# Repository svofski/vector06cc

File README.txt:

VECTOR-06C FPGA REPLICA
	~~~~~~~~~~~~~~~~~~~~~~~

This project is an attempt to replicate Vector-06C, a Soviet-era home 
computer, in FPGA. The primary hardware platform for this project is 
Altera DE1 development board.

CONTENTS

* Features
* DE1 Thingies
* DE1 SRAM Mapping and Starter Kit Utility
* Known Problems
* Known ROMs That Have Issues
* Acknowledgements

Features
~~~~~~~~

The following features are implemented as of December 16, 2007:

- CPU
- SRAM is used for everything
- 8253 timer (not entirely, only what's useful for sound generation)
- tape i/o (and beeper)
- all internal stuff, video modes, palette
- PS/2 keyboard
- 256K RAM disk
- DE1 JTAG interface to JTAG USB API program

DE1 Thingies
~~~~~~~~~~~~

Enjoy the generous blinkenlights from Terasic and svofski!

It is important to have switches SW8 and SW9 in "1" position (up). This
enables proper CPU clocking. Other switches just change the blinken pattern
and only important when you're debugging.

KEY0 is master reset, somewhat like BLK+VVOD. 

KEY1 is manual clock for CPU. Useful only for hardcore debugging.

KEY3 is same as BLK+SBR: boot ROM is disabled, RST0 is executed.

If KEY3 is held pressed when KEY0 is being pressed, or when Vector-06C 
image is being programmed into FPGA, boot ROM doesn't work at all. 
This is useful if you want to preserve SRAM content.

DE1 SRAM Mapping
~~~~~~~~~~~~~~~~
DE1 SRAM is addressed by word. This is mapped linearly into bytes, so programs
can be uploaded with CII Starter Kit Control Panel software without any 
modifications. However, addresses should be minded.

Normally a .rom file goes to address 0x0100. Translated into word-address, that
becomes 0x0080. So when uploading a .rom file to Vector, enter "80" in the SRAM
page, "Sequential Write" box.

Similarly, RAM disk pages start after first 64K, which is 0x10000, or 0x8000 
in words. So, for uploading RAM disk images, use address "8000". RAM disk images
can be read Starter Kit Control Panel software and re-uploaded later or used
with an emulator as .edd files.

Known Problems
~~~~~~~~~~~~~~

1. Keyboard input gets stuck when some of the ":()*@" characters are entered.

	This is a problem with PS/2 -> Vector keyboard key/char mapping.
	I tried to make it as much PS/2 as possible. But since some characters
	shift/key combination differ, there's more than one direct mapping and
	this mapping gets stuck.
	
	Workaround: always carefully press SHIFT, then ":", then release ":", 
	then release SHIFT. If input gets stuck, unstuck it by carefully 
	pressing same character again.

2. PS key is not implemented

	Well, duh.. 

3. BLK+VVOD is not implemented

	Use KEY0 instead.

4. AY-3-WTF is not implemented

n-1. ROM "<whatever>.rom" doesn't work
	
	Unless you know for sure that it must work, screw it.

n. ROM "<whatver>.rom" works incorrectly.

	If you know for sure how it must work, I'm open for suggestions.

Known ROMs That Have Issues
~~~~~~~~~~~~~~~~~~~~~~~~~~~
81dca11bea7fb69a1226a170f1f47e85 *EXOLON.ROM
		Jerky border and keyboard input doesn't work, no known workaround

b27de9107eba6a1d9fb43e92e281099e *MUSICIAN.ROM
		Vertical scrolling is screwed up, depends on keys pressed.
		I studied the code and can't see how it can behave differently.

Acknowledgements
~~~~~~~~~~~~~~~~

This project uses work of different people. 

T80 CPU by Daniel Wallner with fixes from MikeJ of www.fpgaarcade.com is used 
for KR580WM80A. The code is modified in attempt to make this otherwise
excellent CPU cycle-compatible with i8080 and to implement STACK signal in PSW.

82C55 code by MikeJ of www.fpgaarcade.com is used without any modifications.

DE1-specific code uses, or may be based upon, samples from Altera DE1 package.

Special thanks to Alexander Timoshenko for documentation and general information
about Vector-06C, Dmitry Tselikov for hints and good reference emulator, Roman
Panteleev and Artem Navalon for ve27a with debugger.

$Id$

Viacheslav Slavinsky
http://sensi.org/~svo
http://sensi.org/~svo/vector06c

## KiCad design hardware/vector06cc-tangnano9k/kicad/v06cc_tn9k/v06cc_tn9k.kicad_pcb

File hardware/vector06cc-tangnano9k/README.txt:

vector06cc-specific carrier board for Tang Nano 9k

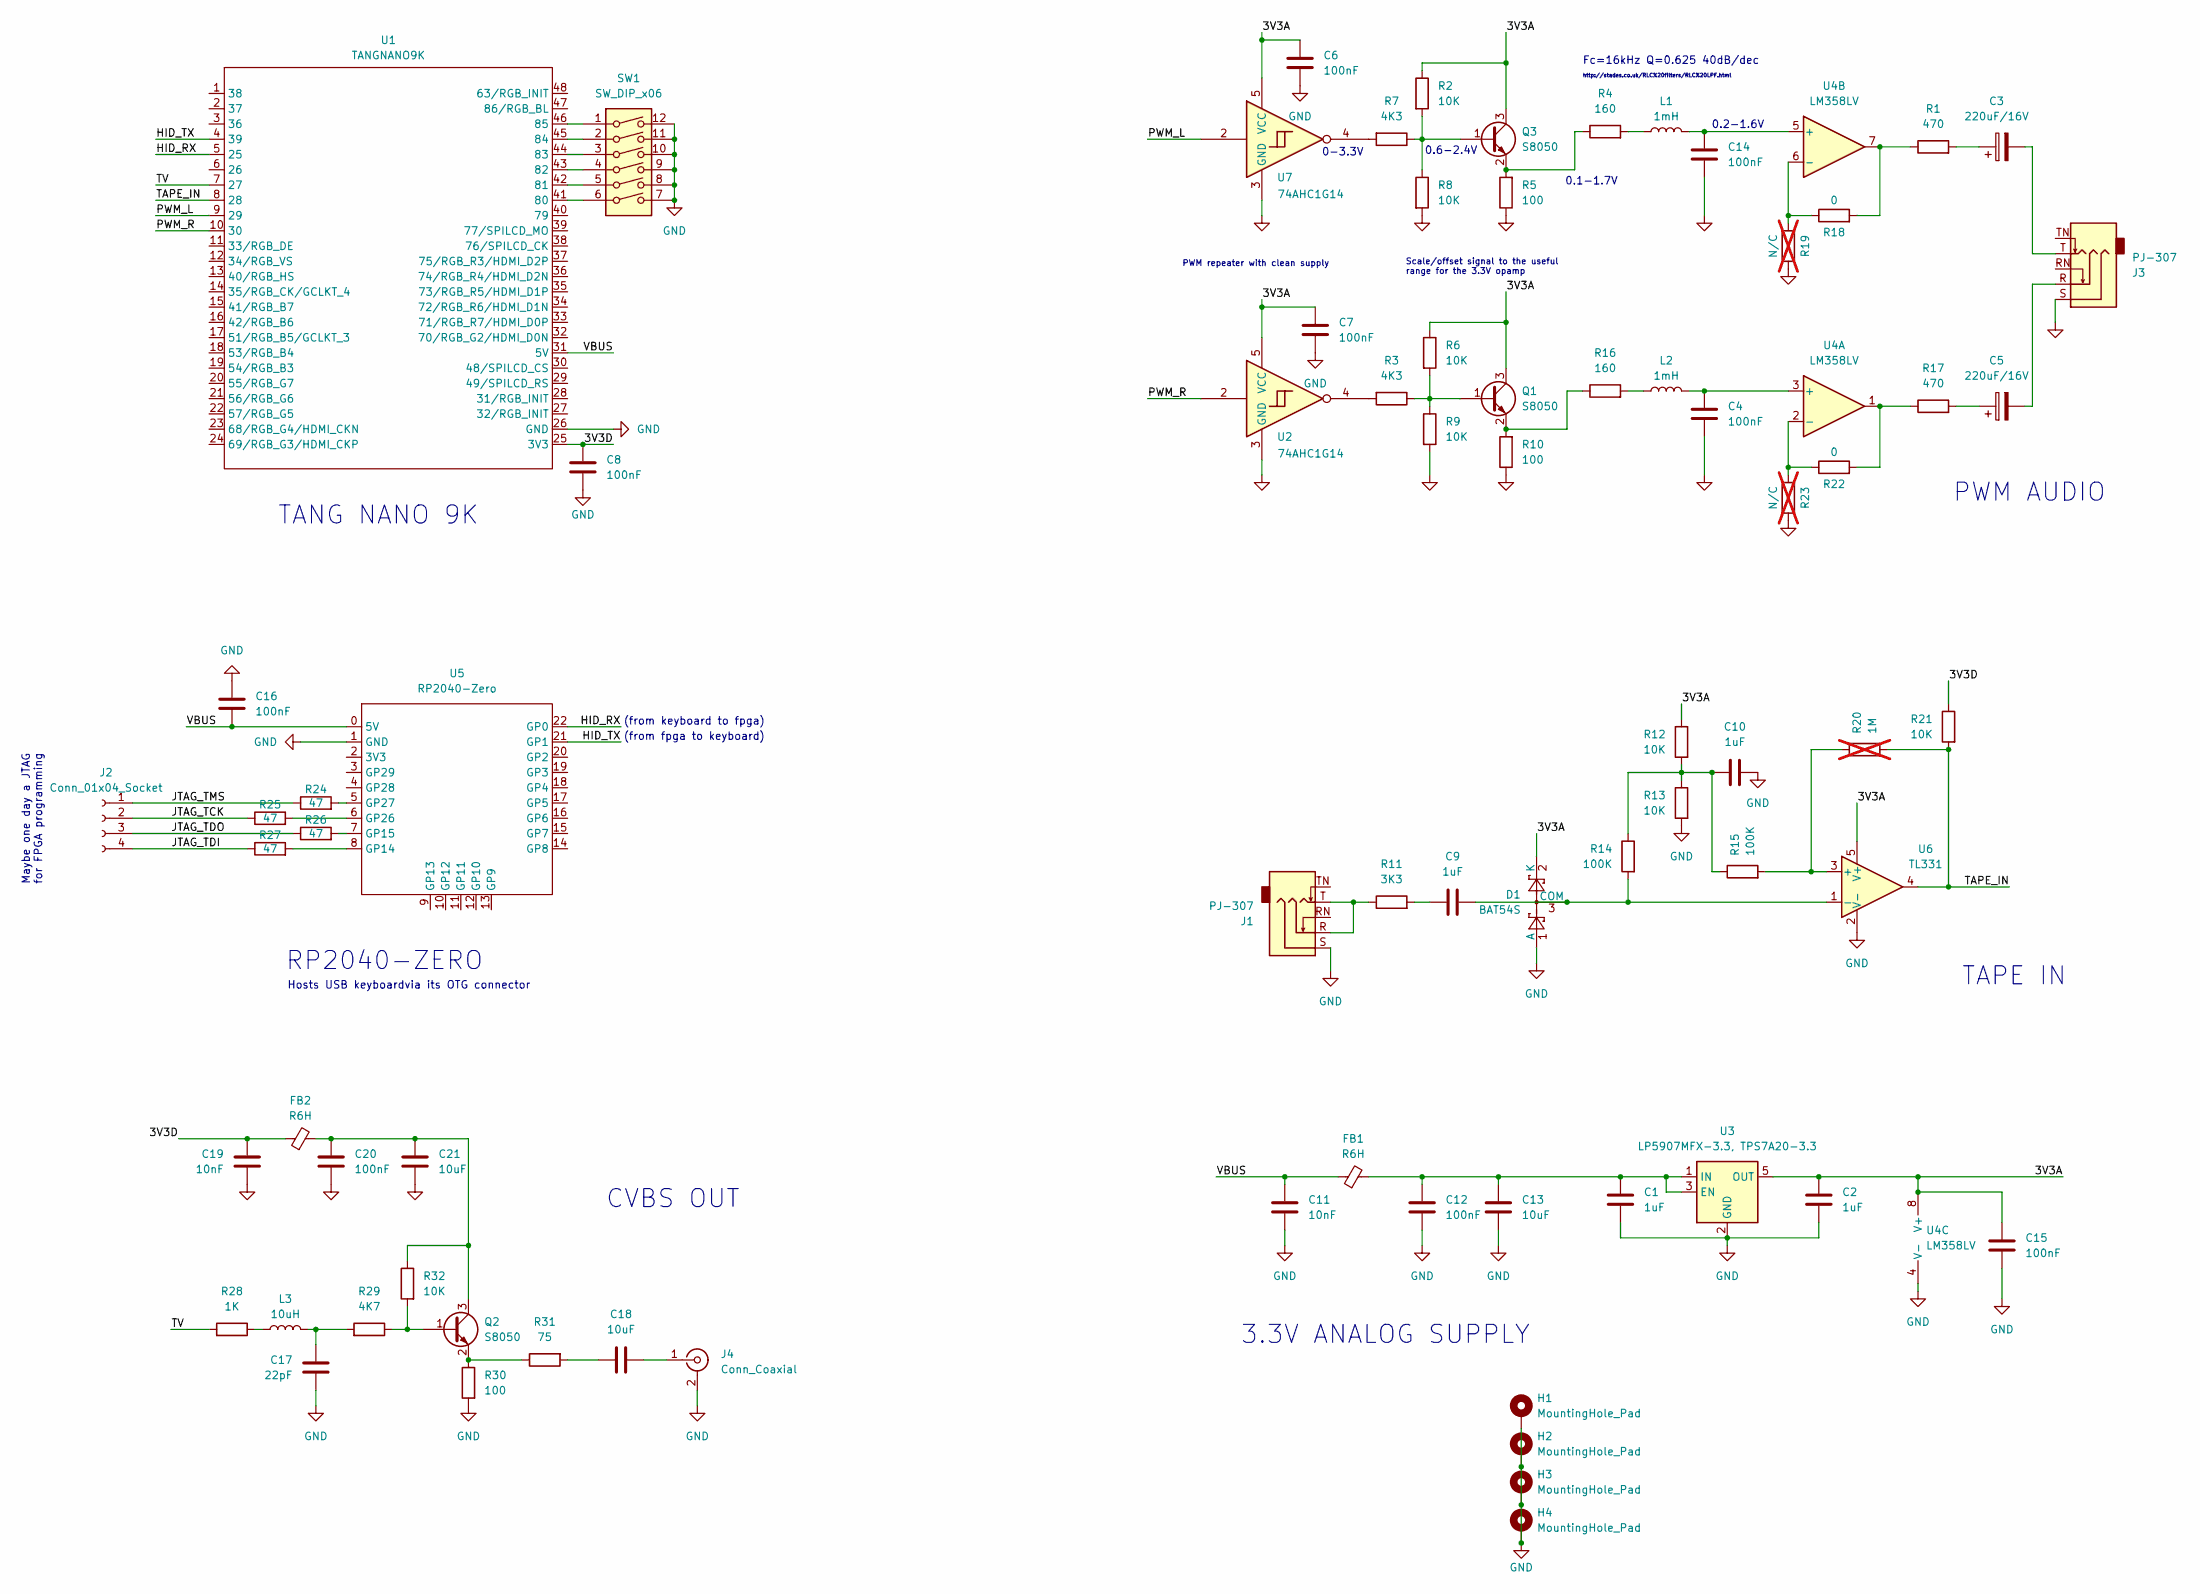
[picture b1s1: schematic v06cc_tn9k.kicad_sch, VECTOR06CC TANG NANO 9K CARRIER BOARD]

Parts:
C1, C2, C9, C10: 1uF; C_0805_2012Metric
C3, C5: 220uF/16V; CP_Elec_6.3x7.7
C4, C6, C7, C8, C12, C14, C15, C16, C20: 100nF; C_0603_1608Metric
C11, C19: 10nF; C_0805_2012Metric
C13, C18, C21: 10uF; C_0805_2012Metric
C17: 22pF; C_0603_1608Metric
D1: BAT54S; SOT-23
FB1, FB2: R6H; L_Radial_D6.0mm_P4.00mm
H1, H2, H3, H4: MountingHole_Pad; MountingHole_3.2mm_M3_DIN965_Pad
J1, J3: PJ-307; Jack_3.5mm_CUI_SJ1-3525N_Horizontal
J2: Conn_01x04_Socket; PinSocket_1x04_P2.54mm_Vertical
J4: Conn_Coaxial; CUI_RCJ-013
L1, L2: 1mH; L_Radial_D7.2mm_P3.00mm_Murata_1700
L3: 10uH; L_0805_2012Metric
Q1, Q2, Q3: S8050; SOT-23
R1, R17: 470; R_0805_2012Metric
R2, R6, R8, R9, R12, R13, R21, R32: 10K; R_0805_2012Metric
R3, R7: 4K3; R_0805_2012Metric
R4, R16: 160; R_0805_2012Metric
R5, R10, R30: 100; R_0805_2012Metric
R11: 3K3; R_0805_2012Metric
R14, R15: 100K; R_0805_2012Metric
R18, R22: 0; R_0805_2012Metric
R19, R23: N/C; R_0805_2012Metric; not fitted
R20: 1M; R_0805_2012Metric; not fitted
R24, R25, R26, R27: 47; R_0805_2012Metric
R28: 1K; R_0805_2012Metric
R29: 4K7; R_0805_2012Metric
R31: 75; R_0805_2012Metric
SW1: SW_DIP_x06; SW_DIP_SPSTx06_Slide_9.78x17.42mm_W7.62mm_P2.54mm
U1: TANGNANO9K; TangNano9k
U2, U7: 74AHC1G14; SOT-23-5
U3: LP5907MFX-3.3, TPS7A20-3.3; SOT-23-5
U4: LM358LV; SOIC-8_3.9x4.9mm_P1.27mm
U5: RP2040-Zero; rp2040-zero
U6: TL331; SOT-23-5

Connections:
/3V3A: C2.1, C6.2, C7.2, C15.2, D1.2 (K), Q1.3 (C), Q3.3 (C), R2.1, R6.1, R12.1, U2.5 (VCC), U3.5 (OUT), U4.8 (V+), U6.5 (V+), U7.5 (VCC)
/3V3D: C8.2, C19.1, FB2.1, R21.1, U1.25 (3V3)
/HID_RX: U1.5 (25), U5.22 (GP0)
/HID_TX: U1.4 (39), U5.21 (GP1)
/JTAG_TCK: J2.2, R25.1
/JTAG_TDI: J2.4, R27.1
/JTAG_TDO: J2.3, R26.1
/JTAG_TMS: J2.1, R24.1
/PWM_L: U1.9 (29), U7.2
/PWM_R: U1.10 (30), U2.2
/TAPE_IN: R20.2, R21.2, U1.8 (28), U6.4
/TV: R28.2, U1.7 (27)
/VBUS: C11.1, C16.1, FB1.1, U1.31 (5V), U5.0 (5V)
GND: C1.2, C2.2, C4.1, C6.1, C7.1, C8.1, C10.2, C11.2, C12.2, C13.2, C14.1, C15.1, C16.2, C17.1, C19.2, C20.2, C21.2, D1.1 (A), H1.1, H2.1, H3.1, H4.1, J1.S, J3.S, J4.2 (Ext), R5.1, R8.2, R9.2, R10.1, R13.2, R19.1, R23.1, R30.2, SW1.7, SW1.8, SW1.9, SW1.10, SW1.11, SW1.12, U1.26 (GND), U2.3 (GND), U3.2 (GND), U4.4 (V-), U5.1 (GND), U6.2 (V-), U7.3 (GND)
unnamed: C3.1, R1.2
unnamed: C3.2, J3.T
unnamed: C5.1, R17.2
unnamed: C5.2, J3.R
unnamed: C9.1, R11.2
unnamed: C10.1, R12.2, R13.1, R14.1, R15.1
unnamed: C17.2, L3.1, R29.2
unnamed: C18.1, R31.2
unnamed: C9.2, D1.3 (COM), R14.2, U6.1 (-)
unnamed: J1.R, J1.T, R11.1
unnamed: C18.2, J4.1 (In)
unnamed: L1.1, R4.2
unnamed: L2.1, R16.2
unnamed: L3.2, R28.1
unnamed: Q1.1 (B), R3.1, R6.2, R9.1
unnamed: Q1.2 (E), R10.2, R16.1
unnamed: Q2.1 (B), R29.1, R32.2
unnamed: C20.1, C21.1, FB2.2, Q2.3 (C), R32.1
unnamed: Q2.2 (E), R30.1, R31.1
unnamed: Q3.1 (B), R2.2, R7.1, R8.1
unnamed: Q3.2 (E), R4.1, R5.2
unnamed: R1.1, R18.2, U4.7
unnamed: R3.2, U2.4
unnamed: R7.2, U7.4
unnamed: R17.1, R22.2, U4.1
unnamed: SW1.6, U1.41 (80)
unnamed: SW1.5, U1.42 (81)
unnamed: SW1.4, U1.43 (82)
unnamed: SW1.3, U1.44 (83)
unnamed: SW1.2, U1.45 (84)
unnamed: SW1.1, U1.46 (85)
unnamed: C1.1, C12.1, C13.1, FB1.2, U3.1 (IN), U3.3 (EN)
unnamed: C4.2, L2.2, U4.3 (+)
unnamed: R22.1, R23.2, U4.2 (-)
unnamed: C14.2, L1.2, U4.5 (+)
unnamed: R18.1, R19.2, U4.6 (-)
unnamed: R27.2, U5.8 (GP14)
unnamed: R26.2, U5.7 (GP15)
unnamed: R25.2, U5.6 (GP26)
unnamed: R24.2, U5.5 (GP27)
unnamed: R15.2, R20.1, U6.3 (+)

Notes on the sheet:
PWM AUDIO
Hosts USB keyboardvia its OTG connector
(from keyboard to fpga)
http://stades.co.uk/RLC%20filters/RLC%20LPF.html
Maybe one day a JTAG for FPGA programming
3.3V ANALOG SUPPLY
0.6-2.4V
0.2-1.6V
Scale/offset signal to the useful range for the 3.3V opamp
PWM repeater with clean supply
(from fpga to keyboard)
0.1-1.7V
RP2040-ZERO
Fc=16kHz Q=0.625 40dB/dec
TAPE IN
0-3.3V
CVBS OUT
TANG NANO 9K

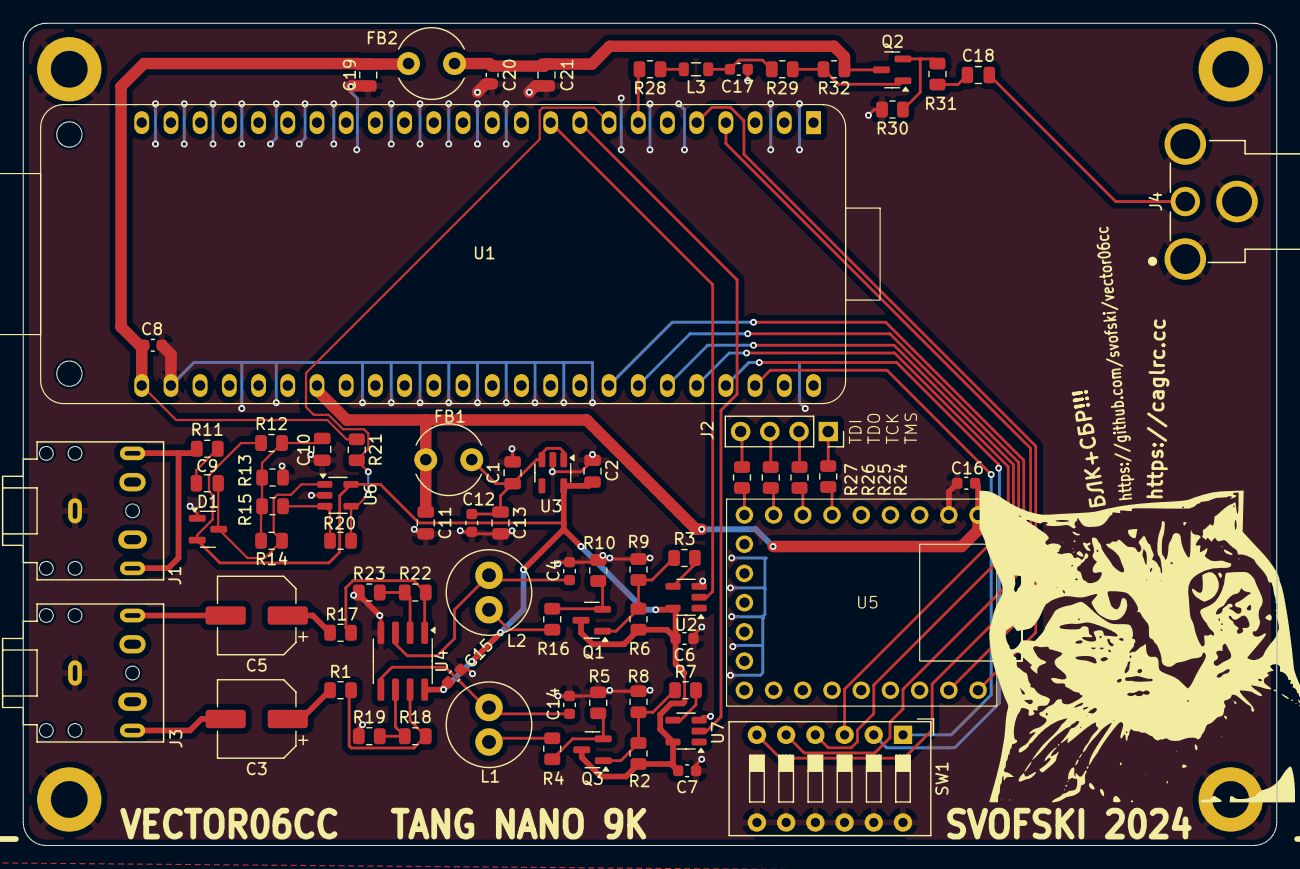
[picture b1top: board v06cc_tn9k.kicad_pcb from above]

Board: 2 copper layers, 109.0 x 71.5 mm, 78 parts (0 on the bottom side), 55 nets.

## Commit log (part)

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2008-01-26 fill last page of file selector
2008-01-26 Edited wiki page through web user interface.
2008-01-27 compilable without floppy or osd
2008-01-29 in i82c55 -- uncommented port clear on mode set; musician.rom doesn't jump its screen then, can't be 100% sure about the rest ay -- fixed reading from registers moved out fake 8255 "pu" to a separate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
2008-01-30 added second PLL to make clean 1.75MHz for AY
2008-01-31 DMA! Very fast floppy now. Instantaneous.
2008-01-31 crop
2008-01-31 testing svg
2008-01-31 Created wiki page through web user interface.
2008-02-02 New cool pics
2008-02-08 + wd1793 status bit 7:notready now indicates presence of SD card in slot (a posterior) + in CPU_STATUS bit 2:crc (rw error) and bit 3:notready (media removed) + sw23 == 2'b10 shows actual floppy stat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
    Firmware:
    + support bits 2,3 in the status word
    + recover after a wrong/empty image file was selected (e.g. after sd card removal)
2008-02-08 poll mmc card presence
2008-02-11 DMA for disk write ops
2008-02-12 dma_read -> dma_rw added multisector write, untested just like multisector read..
2008-02-19 write mode:
    rewrote state machines, added a lot of states to wd1793, mostly to make operation more transparent;
    write works (except for the infamous D>Q in large directories); c compilation test passes.
    still needs a major review before calling complete.
    the host still loves to call abort ($D0) during write operation for some reason; probably it has to do
    with BUSY status and can only be workarounded, as it now is: slave.c saves the current command and
    reuses it later instead of relying on register content.
2008-02-22 $D0 command: reset cmd_mode to 0, clear error bits only when state == STATE_READY --> D>Q works!
2008-02-22 uncommented ay/8253
2008-02-23 Some workarounds for the keys that have different matrix positions depending on shift status.
2008-02-24 key ` enters ` !
2008-02-28 wd1793 docs
2008-02-28 wd docs
2008-08-27 fixed all stack instructions to generate proper STACK cycles SkyNet demo now works flawlessly! implemented but left out rudimentary breakpoint device qsf file now adjusted to QII WE 8.0sp1 configurat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
2008-08-27 port C bits 3:0 should read as '1', this fixes Kolobiha
2009-08-12 mode 0 fixed
2009-09-03 Basic composite output on VGA connector.
    When SW5 is ON:
    VGA.HSYNC = SYNC
    VGA.R = VIDEO
    When SW5 is OFF VGA connector works as usual.
    No PAL encoder and the intensities are false, to be done yet.
2009-09-15 R,G,B joined in one signal to drive signle CVSB wire, SW5 = 1 --> CVSB, SW5 == 0 --> VGA
2009-09-15 forgotten files
2009-09-16 Fixed OSD to be in screen area in TV mode.
2009-09-16 TV feature added to README
2009-09-18 T80/8080 Mode (Mode 2) CPU Fixes: 1. ALU-based subtractions have AC flag inverted, SUB/SBB/DCR... 2. RRC/RLC/RAL/RAR only modify C flag 3. STC/CMC/CMA do not change AC flag 4. ALU AND operation sets 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
    The fixes above make this core pass all known 8080 CPU tests.
    Results of 8080 Executioner match those of real CPU, tested on Vector-06c with KR580VM80A.
    Audio clocks are generated by another PLL for the time being: tape loading didn't work otherwise.
2009-09-20 warp mode 12 (6) MHz with floppy support
2009-10-01 1) 2pi/8 clock step for PAL encoder: saturation, no field interleave (leave SW4=off) 2) adjusted the clock drum to match IRL v06c (tested by raster effects on real), timer CE adjusted accordingly 3) 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
2009-10-01 simulation and clocks picture
2009-10-04 dirty but working fixes for all modes
2009-10-28 1) scroll register update timing: matching with the Tru 2) cpu waitstate generation: changed cputime to wsrom==5 and adjusted palette_wren accordingly
2010-05-15 ...comments only
2011-03-07 1) added ce6x that runs at 1 mclk earlier: this allowed to make address selection in video.v on posedge 2) fixed palette in 512x256 mode 3) used named ports in palette_ram instantiation
2011-03-08 reverted to negedge in pixel pusher because of regress with tv output
2011-03-13 vm1 brutally squeezed into the rib cage, nothing works so far
2011-03-14 makefile and linker scripts..
2013-08-04 dumping some experiments pending for a couple of years
2014-01-06 Revised version that should be compatible with newer DE1 boards with slow SRAM: * registered rom_access to reduce propagation delay on SRAM_OE_N (should be around 8.6 relative to clk50) * big clean u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
2014-02-11 ivagor's sdram port
2014-02-11 +buttrom, zagr512
2014-02-12 Warp mode for SDRAM version (SDRAM at 120 MHz now), compatibility with Z80
2014-02-17 It's like 394 with minor changes in memory access. Something like warp (3 MHz with no waitstates) added.
2014-02-18 COVOX added
2014-03-10 Stereo AY, read from AY works now. Only one base clock 50 MHz used for all purposes.
2014-03-10 Good warp (almost 6 MHz) now, SDRAM works at 60 MHz
2014-03-11 vector06cc.v minor clean-up
2014-05-05 R-Sound support added. Sound codec now works in DSP mode with 12 MHz clock - no more funny sounds in SKYNET. Some switches (SW6/7/9) now unused.
2014-07-07 port to WXEDA Cyclone IV board with SDRAM
2014-07-07 vector06cc runs on wxeda, shows vga output, sdram ok
2014-07-08 +SD card/floppy +PWM beeper sound (horrible)
2014-07-08 project branch cleanup
2014-07-14 updated floppy firmware for new cc65 compiler version, floppy firmware recompiled
2014-07-14 +automatic cc65 builder
2014-07-14 floppy update fixed serial port assignments
2014-07-16 * s-video output on separate pins (pwm) * some compromises in OSD which makes it simultaneously usable on both VGA and TV * R-Sound support made optional
2014-07-16 increase to max driving strength for S-Video pins and decrease to min for VGA pins, this reduces the interference a little bit
2014-07-16 + vector.inc
2014-07-16 - separated border_delay into a module - changed it to be clocked by main clock with ce6, reduced shift depth by 1: appears to be a perfect match to bord.rom picture
2014-07-19 tabs to spaces
2014-07-19 adjusted composite (pwm) out to work with new changes
2014-07-21 some dpf wtf
2014-07-21 backported composite and s-video updates from wxeda-cycloneiv
2014-07-27 pal coefficients for 16xFsc
2014-08-14 + missing files as requested in #44
2014-10-02 Component video output (576p50) added. Selection of VGA/TV modes with SW5:SW4, see comments in beginning of vector06cc.v for details.
2014-10-11 START-1200 on conditional compilation
2015-03-14 Create gh-pages branch via GitHub
2015-03-14 Update index.html
    fixed links
2016-01-30 mixing fixes by ivagor
2016-02-04 Makefile
2016-02-06 buildable cc65 as submodule
2016-02-06 zagr512
2016-02-06 Preparing for easier merging with sdram
2016-02-06 buildable cc65 as submodule
    resolved Conflicts:
    build/Makefile
    firmware/floppysrc/Makefile
    firmware/floppysrc/menu.c
    firmware/floppysrc/slave.c
2016-02-06 sorting project files by board
2016-02-06 Revert "project branch cleanup"
    This partially reverts commit c4d334f0f94bee813a160833f562a0929419fb24, hopefully making it easier to merge back with sdram branch
2016-02-07 merging wxeda with sdram
2016-02-07 three targets compile: de1 de1sram wxeda
2016-02-07 Preparing projects to be usable from Quartus IDE
2016-02-09 verified compilability in quartus ide, works for de1, de1sram, wxeda
2016-02-12 Multiboard version by ivagor See description at http://zx-pk.ru/showthread.php?t=8635&page=48&p=758111&viewfull=1#post758111
2024-04-21 minesweeper mode512 fix
    replaced old 80c55.vhd with b2m's k580vv55.v
    the old version does not support reading from the latch so reading port
    2 reads back 0, which is incorrect.
2024-04-28 vertical scaling to 480 lines, 50hz ok
2024-04-28 F11/F12 support in serial debug probe
2024-05-07 added doc/tangnano9k
2024-05-11 floppy works
    but it's terrible
    had to add hacks special for Gowin
    couldn't use Arlet's 6502 because Gowin hates it
    builds are rather unstable
2024-05-17 Arlet 6502 works
    but can't remove dma, reasons unknown. everything blacks out
2024-05-18 works with gao, doesn't work without. sigh.
2024-05-21 disk/osd is healthy
    still weird how everything can go completely dead because of a slightest
    change.
    menu, file selection, vram read works
    there are traces of attempts to change vram to single-port
2024-05-23 8253 + AY seem to work, untested
    the floppy boots with both options on, but haven't checked the sound
2024-05-31 osd + floppy ok
    - connected the osd buffer, some fixes in the code here and there, all
    good
    - vm80a turns out to be problematic yet, the timings are not correct
    which breaks multicolor
2024-06-01 vm80a works with correct timings
2024-06-06 added project_process_config.json
    because apparently this is where top level entity and some other important
    parameters are defined
2024-06-06 added vector06cc.sdc
2024-08-14 big osd, pwm stereo, pipico hid keyboard
2024-08-14 pipico hid adapter
2024-08-16 audio improvements
    updated pwm clock to 72mhz
    pwm resolution increased to 10 bits
    moved pwm gpio to the 3v3 bank, preferred for driving 3v3 external logic
2024-08-17 updated header info
2024-08-18 rom loading works!
    there seem to be some problems:
    * you need to f1+f11 reset for some roms, probably has to do with
    clearing memory
    * F11 sometimes locks up
    * the list of files seems to be short, maybe a tff problem?
2024-08-20 updates to menu/file selector
    working towards multiple pages for different file types, .fdd and .rom
    at first.
    added linux console simulation for the tui, make and run sim from the
    sim dir
2024-08-21 file selection multiple tabs
    they seem to work well in simulation
2024-08-23 changed timer sampling -> sound quality improved
    8253 was sampled really roughly for the low samplerate codecs
    sigma-delta modulator doesn't need this so we take the current value of
    8253 output, and it sounds amazing in programs that make good use of the
    timer. examples: pwm18i2 (and other pwm sound tests),
    fatax/cronex/bolder and other players by Novikov.
2024-08-25 wav loading works (in principle)
    the details need more work, sample rate is treated a bit too liberally
2024-09-04 vi53 by Sorgelig and b2m
2024-09-04 floppy/wav wip
    16-bit wavs seem to play back ok but korvet-basic still can't load
    bukkakemon
2024-09-05 wav loading works well
    Mostly tested with 8-bit wav files, but bukkakemon is a 16-bit wav and
    it loads in Basic-Korvet. I did not yet test stereo files, but they are
    really an oddity anyway.
    turbo loaders work too
2024-09-06 cas support
    only v06c cas so far
    loaded mandelborat from a cas file into bas299f
    alarm: rom space is running very low, pushing the very top of the available 12K
2024-09-14 wip korvet cas support
    simulation creates loadable data
    verilog side needs a new samplerate (4800), untested yet
2024-09-15 korvet .cas loading works
2024-10-12 relative paths in .gprj
2024-10-12 referenced audio stuff added
2024-10-17 builds, stable with SCAN_5_3
    moved SCAN_2_1, SCAN_5_3, SCAN_7INCH out to config.v
    7-inch next
2024-10-17 OSD is jagged a bit but it's fine
2024-10-17 centered the picture
2024-10-19 psram_controller update, timing at 80.012/0
    changed the state machine to use a full case, apparently it's important
    timing analysis reports clk_psram at 80.012 with zero setup violations
    Important!
    Place option: 1, Clock route order: 1, Route option: 2, Route maxfan: 23
2024-10-19 comment in psram_controller.v
2024-10-20 added hardware README.txt
2024-10-20 synchronize reset with vsync (vga_vs)
    I'm not 100% sure on this. Synchronizing with interrupt pulse appears to
    be coming late, synchronizing with vsync works more reliably.
    Somehow this small change tends to break the timings most severely.
    So no 100% timing closure for now, but it works on the boards that I
    could test.
2024-10-21 hdmi output works (no sound)
    really weird stability problems, but this particular state seems to be
    working well for me.
    simple moving the picture left or right may completely break it.
    psram second phase clock moved to 135 degrees, somehow it helps.
    place-route options are as usual: 1-1-2
    timing constraints are important, even if they are incorrect. there is
